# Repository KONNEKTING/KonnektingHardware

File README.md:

# KonnektingHardware
Schematics and pcb layouts for KONNEKTING devices

There's no common license for all KONNEKTING hardware. Please check each sub-folder for its license.

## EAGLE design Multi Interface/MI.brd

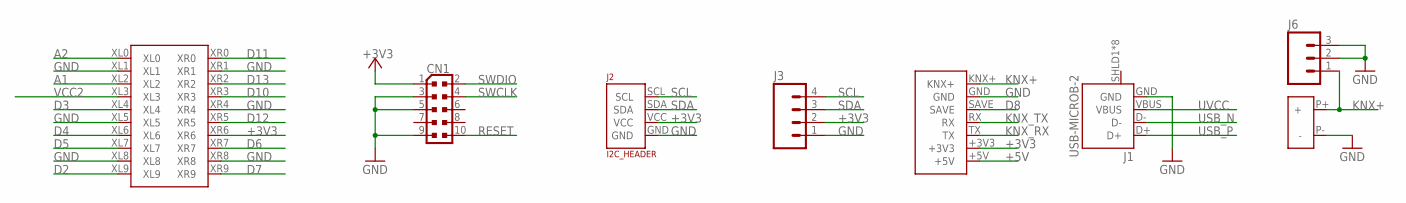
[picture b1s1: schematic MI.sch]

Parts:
CN1: 0171_PH127-205DF055G00AROUND-PADS; PINHEAD_2X05_127
J1: USB-MICROB-2; USB-MICROB-10118194
J2: I2C_HEADER; 4_2.54_11.8X10.2MM
J3: M04NO_SILK_ALL_ROUND; 1X04_NO_SILK_ALL_ROUND
J6: M031X03_NO_SILK; 1X03_NO_SILK
U$1: UFI2; UFI_34X34MM
U$2: KNX_KLEMME
U$3: MICRO_BCU_7_2.54DOCU_D1.4; MICRO_BCU_7_2.54_D1.4_DOCU

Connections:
+3V3: CN1.1, J2.VCC, J3.2, U$1.XR6, U$3.+3V3
+5V: U$3.+5V
A1: U$1.XL2
A2: U$1.XL0
D2: U$1.XL9
D3: U$1.XL4
D4: U$1.XL6
D5: U$1.XL7
D6: U$1.XR7
D7: U$1.XR9
D8: U$3.SAVE
D10: U$1.XR3
D11: U$1.XR0
D12: U$1.XR5
D13: U$1.XR2
GND: CN1.3, CN1.5, CN1.9, J1.GND, J2.GND, J3.1, J6.2, J6.3, U$1.XL1, U$1.XL5, U$1.XL8, U$1.XR1, U$1.XR4, U$1.XR8, U$2.P- (-), U$3.GND
KNX+: J6.1, U$2.P+ (+), U$3.KNX+
KNX_RX: U$3.TX
KNX_TX: U$3.RX
RESET: CN1.10
SCL: J2.SCL, J3.4
SDA: J2.SDA, J3.3
SWCLK: CN1.4
SWDIO: CN1.2
USB_N: J1.D-
USB_P: J1.D+
UVCC: J1.VBUS
VCC2: U$1.XL3

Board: 2 copper layers, 8 parts (3 on the bottom side), 5 nets, no tracks yet.

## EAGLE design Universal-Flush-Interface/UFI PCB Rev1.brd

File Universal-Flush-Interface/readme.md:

# Universal UP Schnittstelle

english version: [readme_en.md](/Universal-Flush-Interface/readme_en.md)

## Lizenz

Die Hardware und Doku dieser Schnittstelle stehen unter folgender Lizenz: [license.md](/Universal-Flush-Interface/license.md)

## Weitere Informationen
[KNX User Forum] (https://knx-user-forum.de/forum/projektforen/konnekting/941633-universal-up-schnittstelle-1wire-up-mini-gateway-bin%C3%A4reing%C3%A4nge-i%C2%B2c-spi-digitale-i-os-etc)

## Teile

|Shop       | Bauteil  | Anzahl | Bestellnummer  |Bezeichnung             |
|:----------|:---------|:-------|:---------------|:-----------------------|
|	Digikey	|	C1,C2	|	2	|	399-8269-1-ND	|	CAP TANT 10UF 16V 10% 1206	|
|	Digikey	|	C32	|	1	|	493-2203-1-ND	|	CAP ALUM 100UF 20% 35V SMD	|
|	Digikey	|	C34	|	3	|	1276-1861-1-ND	|	CAP CER 1UF 35V X5R 0603	|
|	Digikey	|	C35	|	1	|	399-7927-1-ND	|	CAP CER 4700PF 25V X7R 0603	|
|	Digikey	|	C36	|	1	|	1276-1063-1-ND	|	CAP CER 0.047UF 50V X7R 0603	|
|	Digikey	|	C39	|	1	|	2 1276-2407-1-ND	|	CAP CER 10UF 6.3V X5R 0805	|
|	Digikey	|	C4,C5,C21,C31,C37,C38	|	6	|	399-7845-1-ND	|	CAP CER 0.1UF 50V X7R 0603	|
|	Digikey	|	D31	|	1	|	SS16T3GOSCT-ND	|	DIODE SCHOTTKY 60V 1A SMA	|
|	Digikey	|	D32	|	1	|	1SMA40CAT3GOSCT-ND	|	TVS DIODE 40VWM 64.5VC SMA	|
|	Digikey	|	ATMEGA32U4	|	1	|	ATMEGA32U4-MU-ND	|	IC MCU 8BIT 32KB FLASH 44QFN	|
|	Digikey	|	L1	|	1	|	SRR4028-221YCT-ND	|	FIXED IND 220UH 340MA 1.25 OHM	|
|	Digikey	|	Lötstifte	|	2	|	36-1425-2-ND	|	CONN PC PIN CIRC 0.040DIA TIN	|
|	Digikey	|	NCN5120	|	1	|	NCN5120MNTWGOSCT-ND	|	IC RECEIVER/XMITTER KNX 40QFN	|
|	Digikey	|	PROG_LED	|	1	|	475-2815-1-ND	|	LED BLUE DIFFUSED 0603 SMD	|
|	Digikey	|	PROG_SW	|	1	|	450-2146-1-ND	|	SWITCH TACTILE SPST-NO 0.05A 24V	|
|	Digikey	|	R1,R24	|	2	|	RNCP0603FTD10K0CT-ND	|	RES SMD 10K OHM 1% 1/8W 0603	|
|	Digikey	|	R2,R3	|	2	|	311-22.0HRCT-ND	|	RES SMD 22 OHM 1% 1/10W 0603	|
|	Digikey	|	R21	|	1	|	RNCP0603FTD100RCT-ND	| RES SMD 100 OHM 1% 1/8W 0603  |
|	Digikey	|	R22,R23,R26,R27	|	4	|	311-4.70KHRCT-ND	|	RES SMD 4.7K OHM 1% 1/10W 0603	|
|	Digikey	|	R25	|	1	|	311-1.00KHRCT-ND	|	RES SMD 1K OHM 1% 1/10W 0603	|
|	Digikey	|	R35	|	1	|	5 A102515CT-ND	|	RES SMD 22 OHM 5% 1W 2512	|
|	Digikey	|	R36	|	1	|	RNCP0603FTD1R00CT-ND	|	RES SMD 1 OHM 1% 1/8W 0603	|
|	Digikey	|	U1	|	1	|	576-1281-1-ND	|	IC REG LDO 3.3V 0.5A SOT23-5	|
|	Digikey	|	USB	|	1	|	609-4618-1-ND	|	USB - Mikro-B, USB 2,0	|
|	Digikey	|	Y1	|	1	|	490-1195-1-ND	|	CER RES 8.0000MHZ 33PF SMD	|
|	Digikey	|	Y31	|	1	|	490-1198-1-ND	|	CER RES 16.0000MHZ 15PF SMD	|
|	Conrad	|		|	1	|	534298	|	Gehäuse 40x40x20	|
|	Conrad	|		|	2	|	889177	|	Schraube 2.2x4.5mm	|
|	Conrad	|		|	1	|	567891	|	Schraubklemme 10polig	|
|		|		|		|		|		|
|	Conrad	|		|	1+1*	|	567615	|	Schraubklemme 3polig	|
|		|		|		|		|		|
|	Conrad	|		|	1*	|	1088238	|	Stiftleiste	|
|	Conrad	|		|	1*	|	1088237	|	Buchse	|
|	Conrad	|		|	4*	|	1088222	|	Crimpkontakt	|
|		|		|		|		|		|
|	Conrad	|		|	1*	|	567803	|	Schraubklemme 7polig	|
|	Conrad	|		|	1*	|	567658	|	Schraubklemme 4polig	|

*) Man kann zwischen 3 Optionen wählen
- 3-polige Schraubklemme + Stiftleiste/Buchse/Crimpkontakt 
- 3+4-polige Schraubklemme
- 7-polige Schraubklemme

## Schaltung
[Universal Flush Interface.pdf](/Universal-Flush-Interface/Universal Flush Interface.pdf)

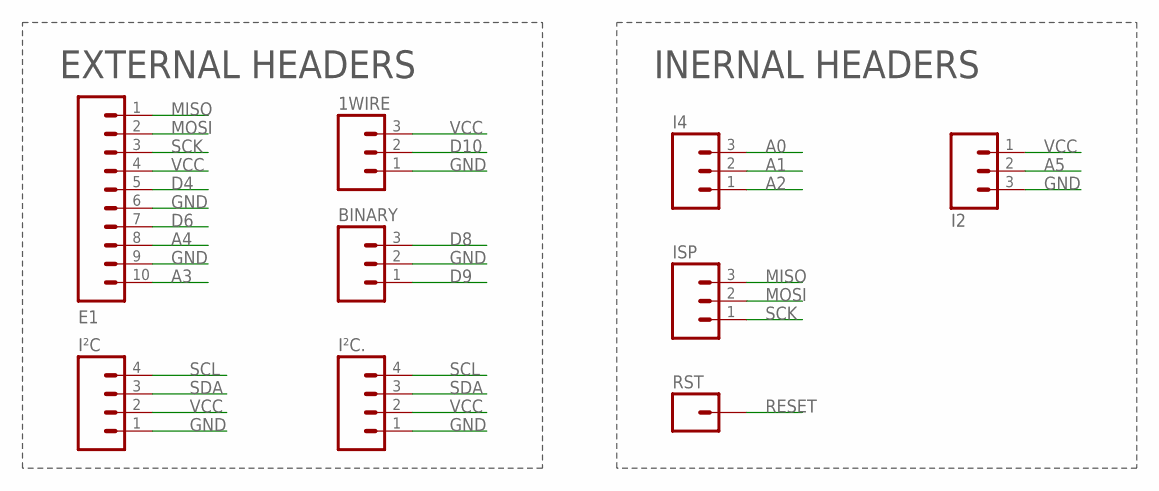
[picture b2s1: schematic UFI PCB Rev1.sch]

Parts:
1WIRE: M031X03_NO_SILK; 1X03_NO_SILK
BINARY: M031X03_NO_SILK; 1X03_NO_SILK
E1: M10NO_SILK_PTH_FEMALE; 1X10_NO_SILK
I2, I4: M031X03_NO_SILK; 1X03_NO_SILK
ISP: M031X03_NO_SILK; 1X03_NO_SILK
I²C, I²C.: M04NO_SILK_ALL_ROUND; 1X04_NO_SILK_ALL_ROUND
RST: M01PTH_NO_SILK_YES_STOP; 1X01_NO_SILK

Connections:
A0: I4.3
A1: I4.2
A2: I4.1
A3: E1.10
A4: E1.8
A5: I2.2
D4: E1.5
D6: E1.7
D8: BINARY.3
D9: BINARY.1
D10: 1WIRE.2
GND: 1WIRE.1, BINARY.2, E1.6, E1.9, I2.3, I²C.1, I²C..1
MISO: E1.1, ISP.3
MOSI: E1.2, ISP.2
RESET: RST.1
SCK: E1.3, ISP.1
SCL: I²C.4, I²C..4
SDA: I²C.3, I²C..3
VCC: 1WIRE.3, E1.4, I2.1, I²C.2, I²C..2

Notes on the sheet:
EXTERNAL HEADERS
INERNAL HEADERS

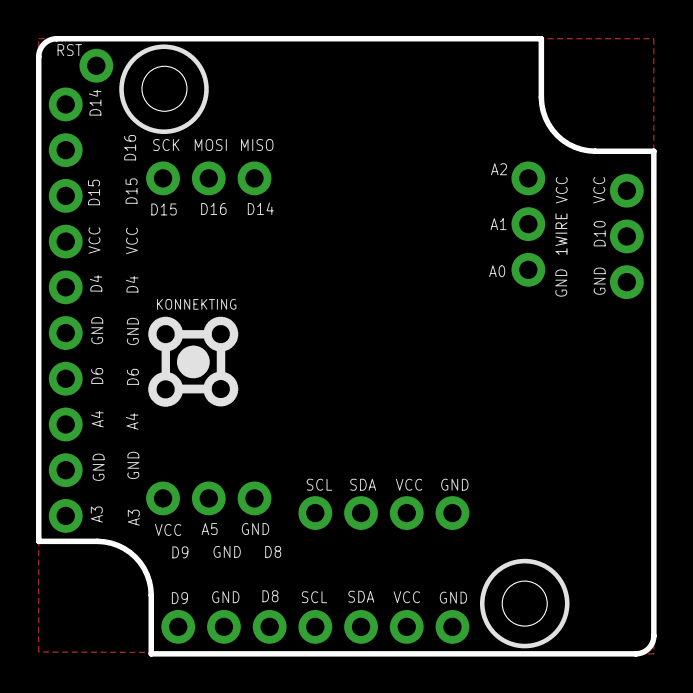
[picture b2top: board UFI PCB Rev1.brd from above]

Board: 2 copper layers, 34.2 x 34.2 mm, 10 parts (0 on the bottom side), 7 nets.

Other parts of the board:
U$1: LOGO_5MM

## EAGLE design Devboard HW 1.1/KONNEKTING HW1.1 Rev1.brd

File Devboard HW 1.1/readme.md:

# Devboard HW 1.1

## License

Hardware and documentation released under this license: [license.md](/Devboard HW 1.1/license.md)

## More infos: 
[konnekting.de](http://www.konnekting.de/projekte/entwicklungsboards/)

## Parts

|Article number        | Part  | Description         | Amount      |
|:------------------|:---------|:--------------------|:-------------|
|	493-2203-1-ND 	|	C7 	|	CAP ALUM 100UF 20% 35V SMD 	|	1	|
|	1276-1063-1-ND 	|	C4 	|	CAP CER 0.047UF 50V X7R 0603 	|	1	|
|	399-7845-1-ND 	|	C6;C9;C11;C15 	|	CAP CER 0.1UF 50V X7R 0603 	|	4	|
|	1276-3013-1-ND 	|	C1;C12 	|	CAP CER 10UF 6.3V Y5V 0805 	|	2	|
|	1276-1861-1-ND 	|	C8 	|	CAP CER 1UF 35V X5R 0603 	|	1	|
|	399-7927-1-ND 	|	C5 	|	CAP CER 4700PF 25V X7R 0603 	|	1	|
|	490-1198-1-ND 	|	Y1 	|	CER RES 16.0000MHZ 15PF SMD 	|	1	|
|	36-1425-2-ND 	|	Pins	|	CONN PC PIN CIRC 0.040DIA TIN 	|	2	|
|	SS16T3GOSCT-ND 	|	D1 	|	DIODE SCHOTTKY 60V 1A SMA 	|	1	|
|	SRR5028-221YCT-ND 	|	L1;L2 	|	FIXED IND 220UH 300MA 1.25 OHM 	|	2	|
|	NCN5120MNTWGOSCT-ND 	|	NCN5120 	|	IC RECEIVER/XMITTER KNX 40QFN 	|	1	|
|	475-2815-1-ND 	|	PROG_LED 	|	LED BLUE DIFFUSED 0603 SMD 	|	1	|
|	RNCP0603FTD1R00CT-ND 	|	R2;R5 	|	RES SMD 1 OHM 1% 1/8W 0603 	|	2	|
|	RNCP0603FTD100RCT-ND 	|	R10_LED_3.3V 	|	RES SMD 100 OHM 1% 1/8W 0603 	|	1	|
|	RNCP0603FTD475RCT-ND 	|	R10_LED_5V 	|	RES SMD 475 OHM 1% 1/8W 0603 	|	1	|
|	RNCP0603FTD10K0CT-ND 	|	R13 	|	RES SMD 10K OHM 1% 1/8W 0603 	|	1	|
|	311-33.0KHRCT-ND 	|	R3_5V 	|	RES SMD 33K OHM 1% 1/10W 0603 	|	1	|
|	311-180KHRCT-ND 	|	R6_5V 	|	RES SMD 180K OHM 1% 1/10W 0603 	|	1	|
|	RNCP0603FTD1K00CT-ND 	|	R7,R8,R9 	|	RES SMD 1K OHM 1% 1/8W 0603 	|	3	|
|	A102515CT-ND 	|	R4 	|	RES SMD 22 OHM 5% 1W 2512 	|	1	|
|	RNCP0603FTD2K00CT-ND 	|	R12 	|	RES SMD 2K OHM 1% 1/8W 0603 	|	1	|
|	311-4.70KHRCT-ND 	|	R1_1WIRE 	|	RES SMD 4.7K OHM 1% 1/10W 0603 	|	1	|
|	450-2146-1-ND 	|	PROG_SW 	|	SWITCH TACTILE SPST-NO 0.05A 24V 	|	1	|
|	1SMA40CAT3GOSCT-ND 	|	D2 	|	TVS DIODE 40VWM 64.5VC SMA 	|	1	|

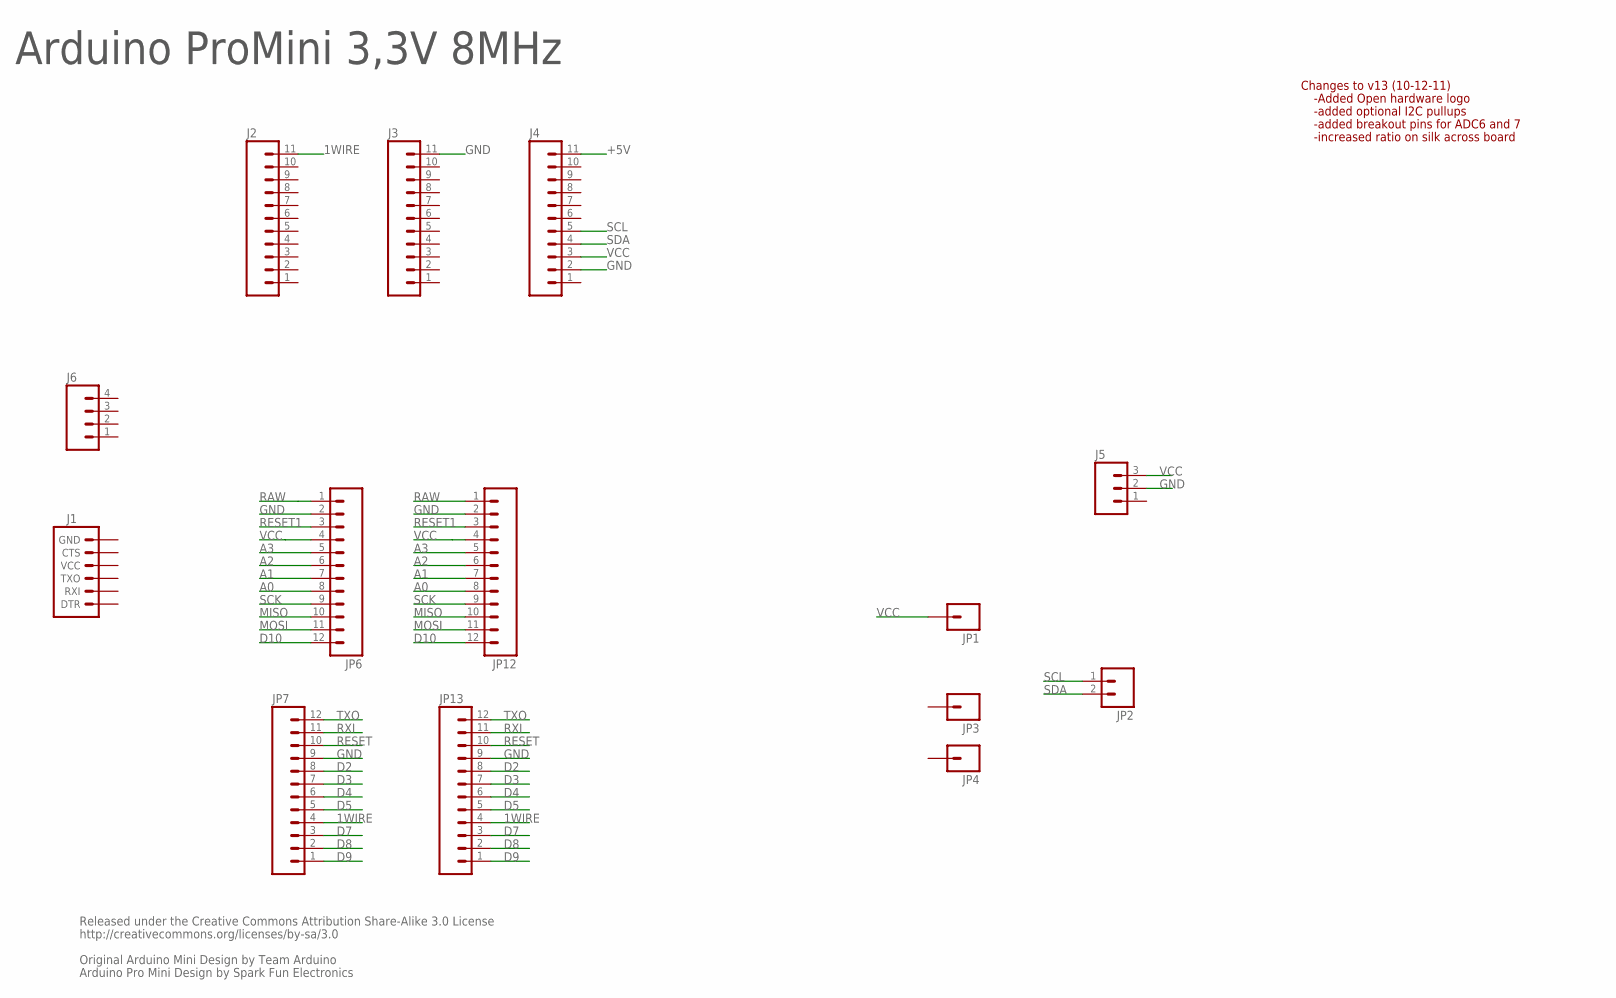
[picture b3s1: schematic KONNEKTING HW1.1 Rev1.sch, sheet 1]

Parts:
J1: ARDUINO_SERIAL_PROGRAMPTH; 1X06
J2, J3, J4: M11PTH; 1X11
J5: M03PTH; 1X03
J6: M04PTH; 1X04
JP1, JP3, JP4: M01PTH; 1X01
JP2: M02PTH; 1X02
JP6, JP7, JP12, JP13: M12PTH; 1X12

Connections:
1WIRE: J2.11, JP7.4, JP13.4; also elsewhere on the board
+5V: J4.11; also elsewhere on the board
A0: JP6.8, JP12.8
A1: JP6.7, JP12.7
A2: JP6.6, JP12.6
A3: JP6.5, JP12.5
D2: JP7.8, JP13.8; also elsewhere on the board
D3: JP7.7, JP13.7; also elsewhere on the board
D4: JP7.6, JP13.6
D5: JP7.5, JP13.5
D7: JP7.3, JP13.3; also elsewhere on the board
D8: JP7.2, JP13.2; also elsewhere on the board
D9: JP7.1, JP13.1; also elsewhere on the board
D10: JP6.12, JP12.12
GND: J3.11, J4.2, J5.2, JP6.2, JP7.9, JP12.2, JP13.9; also elsewhere on the board
MISO: JP6.10, JP12.10
MOSI: JP6.11, JP12.11
RAW: JP6.1, JP12.1
RESET: JP7.10, JP13.10
RESET1: JP6.3, JP12.3
RXI: JP7.11, JP13.11; also elsewhere on the board
SCK: JP6.9, JP12.9
SCL: J4.5, JP2.1
SDA: J4.4, JP2.2
TXO: JP7.12, JP13.12; also elsewhere on the board
VCC: J4.3, J5.3, JP1.1, JP6.4, JP12.4; also elsewhere on the board

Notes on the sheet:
Released under the Creative Commons Attribution Share-Alike 3.0 License
http://creativecommons.org/licenses/by-sa/3.0
Original Arduino Mini Design by Team Arduino
Arduino Pro Mini Design by Spark Fun Electronics
Changes to v13 (10-12-11)
-Added Open hardware logo
-added optional I2C pullups
-added breakout pins for ADC6 and 7
-increased ratio on silk across board
Arduino ProMini 3,3V 8MHz

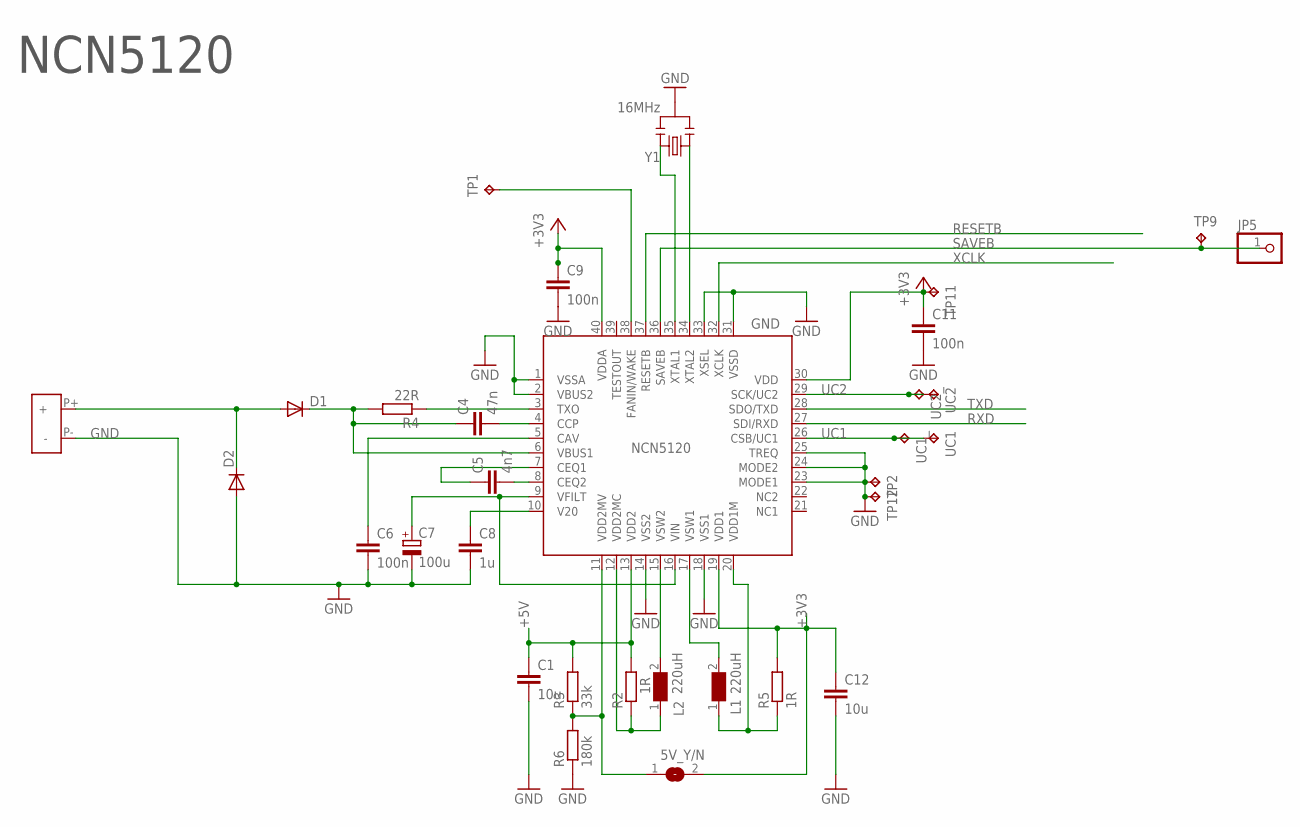
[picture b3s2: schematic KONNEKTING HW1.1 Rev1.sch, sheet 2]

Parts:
5V_Y/N: SJ
C1, C12: 10u; C0805
C4: 47n; C0603
C5: 4n7; C0603
C6, C9, C11: 100n; C0603
C7: 100u; UD-6,3X7,7_NICHICON
C8: 1u; C0603
D1, D2: DIODESMA-ALT; SMA-DIODE_ALT
GND: NCN5120_KNX_TRANSCEIVER; QFN40
JP5: PINHD-1X1; 1X01
L1, L2: 220uH; WE-PD2_7850
R2, R5: 1R; R0603
R3: 33k; R0603
R4: 22R; R2512
R6: 180k; R0603
TP1, TP9: TPTP10SQ; TP10SQ
TP2, TP11, TP12: TPTP09SQ; TP09SQ
U$2: KNX_KLEMME
UC1, UC1_, UC2, UC2_: TPTP09SQ; TP09SQ
Y1: 16MHz; RESONATOR-SMD

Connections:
+3V3: 5V_Y/N.2, C9.1, C11.1, C12.1, GND.19 (VDD1), GND.30 (VDD), GND.40 (VDDA), R5.2, TP11.TP; also elsewhere on the board
+5V: C1.1, GND.13 (VDD2), R2.2, R3.2; also elsewhere on the board
GND: C1.2, C6.2, C7.-, C8.2, C9.2, C11.2, C12.2, D2.A, GND.1 (VSSA), GND.2 (VBUS2), GND.14 (VSS2), GND.18 (VSS1), GND.23 (MODE1), GND.24 (MODE2), GND.25 (TREQ), GND.31 (VSSD), GND.33 (XSEL), R6.1, TP2.TP, TP12.TP, U$2.P- (-), Y1.2; also elsewhere on the board
unnamed: 5V_Y/N.1, GND.11 (VDD2MV), R3.1, R6.2
unnamed: GND.3 (TXO), R4.1
unnamed: C4.1, D1.C, GND.6 (VBUS1), R4.2
unnamed: C5.1, GND.7 (CEQ1)
unnamed: C7.+, GND.9 (VFILT), GND.16 (VIN)
unnamed: GND.15 (VSW2), L2.2
unnamed: C8.1, GND.10 (V20)
unnamed: C6.1, GND.5 (CAV)
unnamed: C4.2, GND.4 (CCP)
unnamed: C5.2, GND.8 (CEQ2)
unnamed: D1.A, D2.C, U$2.P+ (+)
unnamed: GND.38 (FANIN/WAKE), TP1.TP
unnamed: GND.12 (VDD2MC), L2.1, R2.1
unnamed: GND.35 (XTAL1), Y1.3
unnamed: GND.34 (XTAL2), Y1.1
unnamed: GND.17 (VSW1), L1.2
unnamed: GND.20 (VDD1M), L1.1, R5.1
RESETB: GND.37 (RESETB)
RXD: GND.27 (SDI/RXD); also elsewhere on the board
SAVEB: GND.36 (SAVEB), JP5.1, TP9.TP
TXD: GND.28 (SDO/TXD); also elsewhere on the board
UC1: GND.26 (CSB/UC1), UC1.TP, UC1_.TP
UC2: GND.29 (SCK/UC2), UC2.TP, UC2_.TP
XCLK: GND.32 (XCLK)

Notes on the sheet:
NCN5120

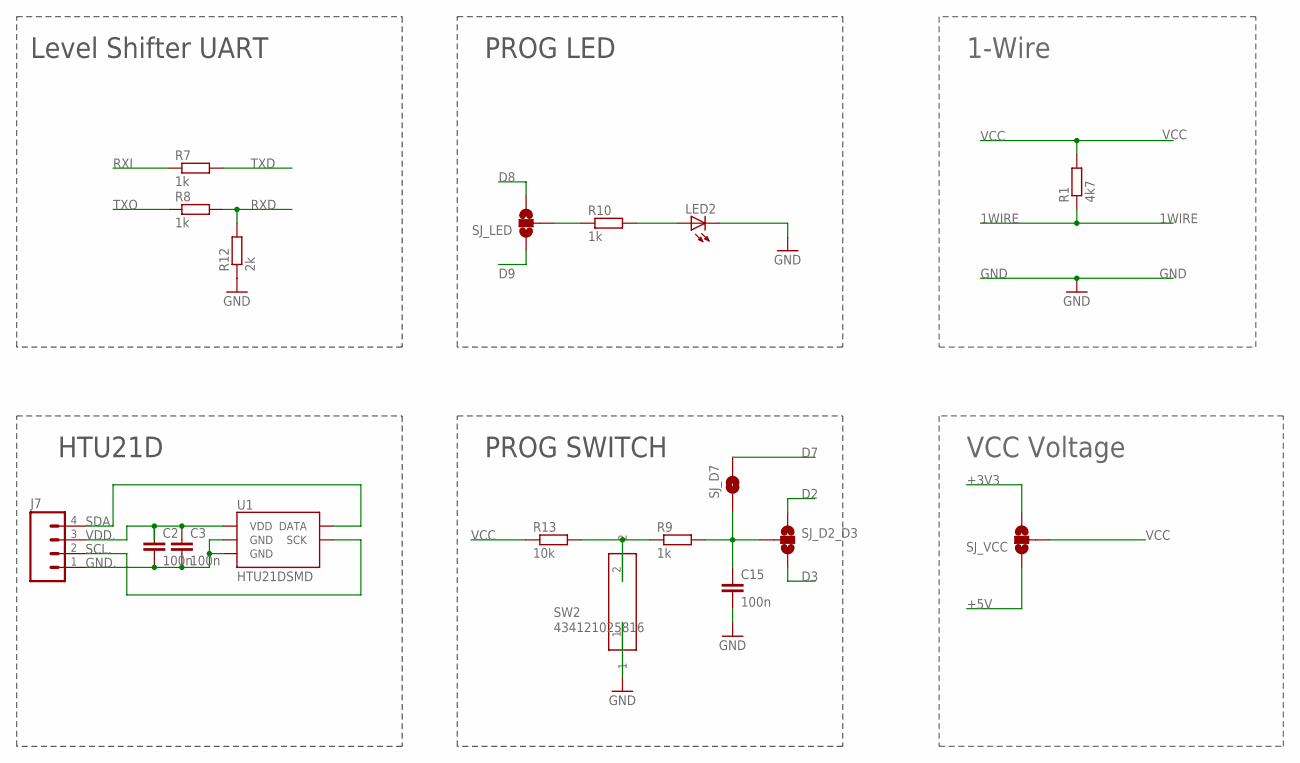
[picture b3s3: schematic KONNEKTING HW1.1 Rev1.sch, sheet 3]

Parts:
C2, C3: 100n; 0603-CAP
C15: 100n; C0603
J7: M04PTH; 1X04
LED2: LEDCHIP-LED0805; CHIP-LED0805
R1: 4k7; R0603
R7, R8: 1k; R0805
R9, R10: 1k; R0603
R12: 2k; R0805
R13: 10k; R0603
SJ_D2_D3: SOLDERJUMPER_2WAYS; SJ_3
SJ_D7: SOLDERJUMPERNO; SJ_2S-NO
SJ_LED: SOLDERJUMPER_2WAYS; SJ_3
SJ_VCC: SOLDERJUMPER_2WAYS; SJ_3
SW2: 434121025816
U1: HTU21DSMD; HTU21D

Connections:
1WIRE: R1.1; also elsewhere on the board
+3V3: SJ_VCC.3; also elsewhere on the board
+5V: SJ_VCC.1; also elsewhere on the board
D2: SJ_D2_D3.1; also elsewhere on the board
D3: SJ_D2_D3.3; also elsewhere on the board
D7: SJ_D7.2; also elsewhere on the board
D8: SJ_LED.3; also elsewhere on the board
D9: SJ_LED.1; also elsewhere on the board
GND: C15.2, LED2.C, R12.1, SW2.1; also elsewhere on the board
GND.: C2.2, C3.2, J7.1, U1.7 (GND), U1.GND
unnamed: R9.1, R13.2, SW2.2
unnamed: LED2.A, R10.2
unnamed: R10.1, SJ_LED.2
unnamed: C15.1, R9.2, SJ_D2_D3.2, SJ_D7.1
RXD: R8.2, R12.2; also elsewhere on the board
RXI: R7.1; also elsewhere on the board
SCL.: J7.2, U1.SCK
SDA.: J7.4, U1.DATA
TXD: R7.2; also elsewhere on the board
TXO: R8.1; also elsewhere on the board
VCC: R1.2, R13.1, SJ_VCC.2; also elsewhere on the board
VDD.: C2.1, C3.1, J7.3, U1.VDD

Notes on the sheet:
Level Shifter UART
PROG LED
HTU21D
PROG SWITCH
1-Wire
VCC Voltage

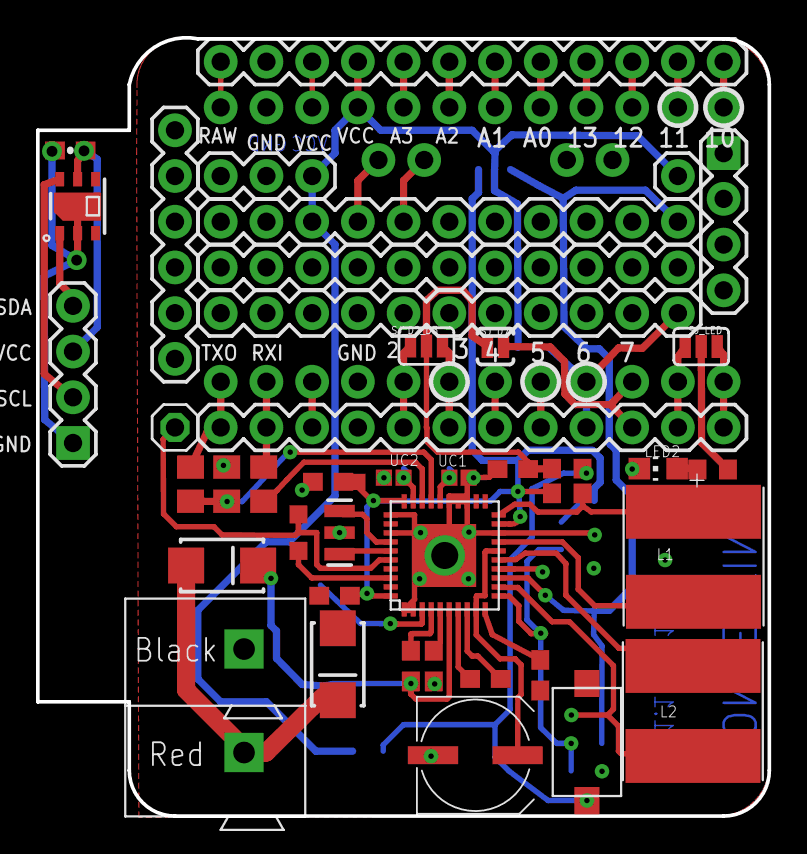
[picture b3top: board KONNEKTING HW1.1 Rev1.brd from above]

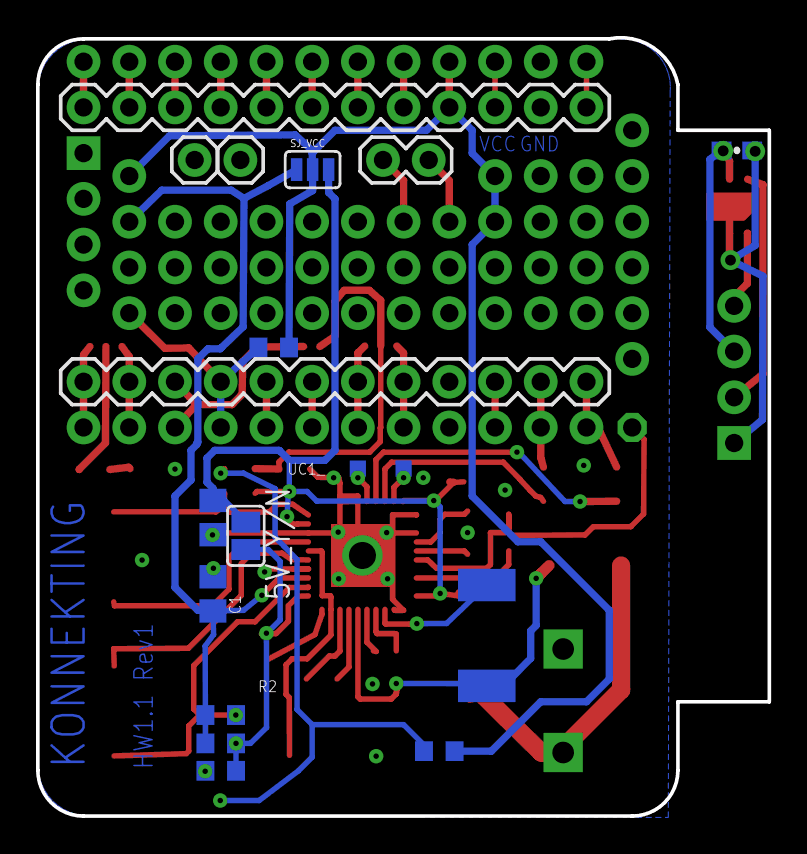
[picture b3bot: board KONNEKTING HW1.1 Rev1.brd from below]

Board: 2 copper layers, 40.6 x 43.2 mm, 64 parts (18 on the bottom side), 57 nets.

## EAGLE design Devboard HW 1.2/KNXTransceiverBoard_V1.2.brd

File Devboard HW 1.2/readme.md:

# Devboard HW 1.2

## License

Hardware and documentation released under this license: [license.md](/Devboard HW 1.2/license.md)

## More infos: 
[konnekting.de](http://www.konnekting.de/projekte/entwicklungsboards/)

## Parts for NCN5120
|Article number        | Part  | Description         | Amount      |
|:------------------|:---------|:--------------------|:-------------|
|	493-2203-1-ND	|	C11	|	CAP ALUM 100UF 20% 35V SMD	|	1	|
|	1276-1063-1-ND	|	C7	|	CAP CER 0.047UF 50V X7R 0603	|	1	|
|	399-7845-1-ND	|	C9;C18;C20;C21	|	CAP CER 0.1UF 50V X7R 0603	|	4	|
|	1276-2407-1-ND	|	C15	|	CAP CER 10UF 6.3V X5R 0805	|	1	|
|	1276-1861-1-ND	|	C4	|	CAP CER 1UF 35V X5R 0603	|	1	|
|	399-7927-1-ND	|	C8	|	CAP CER 4700PF 25V X7R 0603	|	1	|
|	490-1198-1-ND	|	Y1	|	CER RES 16.0000MHZ 15PF SMD	|	1	|
|	36-1425-2-ND	|	Pins	|	CONN PC PIN CIRC 0.040DIA TIN	|	2	|
|	SS16T3GOSCT-ND	|	D1	|	DIODE SCHOTTKY 60V 1A SMA	|	1	|
|	SRR5028-221YCT-ND	|	L1	|	FIXED IND 220UH 300MA 1.25 OHM	|	1	|
|	NCN5120MNTWGOSCT-ND	|	NCN5120	|	IC RECEIVER/XMITTER KNX 40QFN	|	1	|
|	475-2815-1-ND	|	PROG_LED	|	LED BLUE DIFFUSED 0603 SMD	|	1	|
|	RNCP0603FTD1R00CT-ND	|	R3	|	RES SMD 1 OHM 1% 1/8W 0603	|	1	|
|	RNCP0603FTD100RCT-ND	|	R123.3V	|	RES SMD 100 OHM 1% 1/8W 0603	|	1	|
|	RNCP0603FTD10K0CT-ND	|	R14	|	RES SMD 10K OHM 1% 1/8W 0603	|	1	|
|	311-1.00KHRCT-ND	|	R8;R9;R10	|	RES SMD 1K OHM 1% 1/10W 0603	|	3	|
|	A102515CT-ND	|	R1	|	RES SMD 22 OHM 5% 1W 2512	|	1	|
|	450-2146-1-ND	|	PROG_SW	|	SWITCH TACTILE SPST-NO 0.05A 24V	|	1	|
|	1SMA40CAT3GOSCT-ND	|	D2	|	TVS DIODE 40VWM 64.5VC SMA	|	1	|

## Parts for ProMicro

|Article number        | Part  | Description         | Amount      |
|:------------------|:---------|:--------------------|:-------------|
|	399-7845-1-ND 	|	C1;C2;C3 	|	CAP CER 0.1UF 50V X7R 0603 	|	3	|
|	1276-1036-1-ND 	|	C5;C10 	|	CAP CER 1UF 6.3V X5R 0603 	|	2	|
|	399-8269-1-ND 	|	C13;C19 	|	CAP TANT 10UF 16V 10% 1206 	|	2	|
|	490-1195-1-ND 	|	Y3 	|	CER RES 8.0000MHZ 33PF SMD 	|	1	|
|	732-3155-1-ND 	|	USB 	|	CONN RCPT USB MICRO B R/A SMT 	|	1	|
|	NSR0320MW2T1GOSCT-ND 	|	D2 	|	DIODE SCHOTTKY 20V 1A SOD323 	|	1	|
|	507-1876-1-ND 	|	F1 	|	FUSE 500MA 125VAC FAST 1206 	|	1	|
|	ATMEGA32U4-MU-ND 	|	IC 	|	IC MCU 8BIT 32KB FLASH 44QFN 	|	1	|
|	576-1281-1-ND 	|	U2 	|	IC REG LDO 3.3V 0.5A SOT23-5 	|	1	|
|	475-2815-1-ND 	|	LED1 	|	LED BLUE DIFFUSED 0603 SMD 	|	1	|
|	475-2709-1-ND 	|	GREEN 	|	LED GREEN DIFFUSED 0603 SMD 	|	1	|
|	475-1196-1-ND 	|	YELLOW 	|	LED YELLOW DIFFUSED 0603 SMD 	|	1	|
|	RNCP0603FTD100RCT-ND 	|	R11 	|	RES SMD 100 OHM 1% 1/8W 0603 	|	1	|
|	311-10.0KHRCT-ND 	|	R2 	|	RES SMD 10K OHM 1% 1/10W 0603 	|	1	|
|	311-1.0KGRCT-ND 	|	R4;R6 	|	RES SMD 1K OHM 5% 1/10W 0603 	|	2	|
|	311-22.0HRCT-ND 	|	R5;R7 	|	RES SMD 22 OHM 1% 1/10W 0603 	|	2	|
|	CKN9104CT-ND 	|	ResetBtn 	|	SWITCH TACTILE SPST-NO 0.02A 15V 	|	1	|

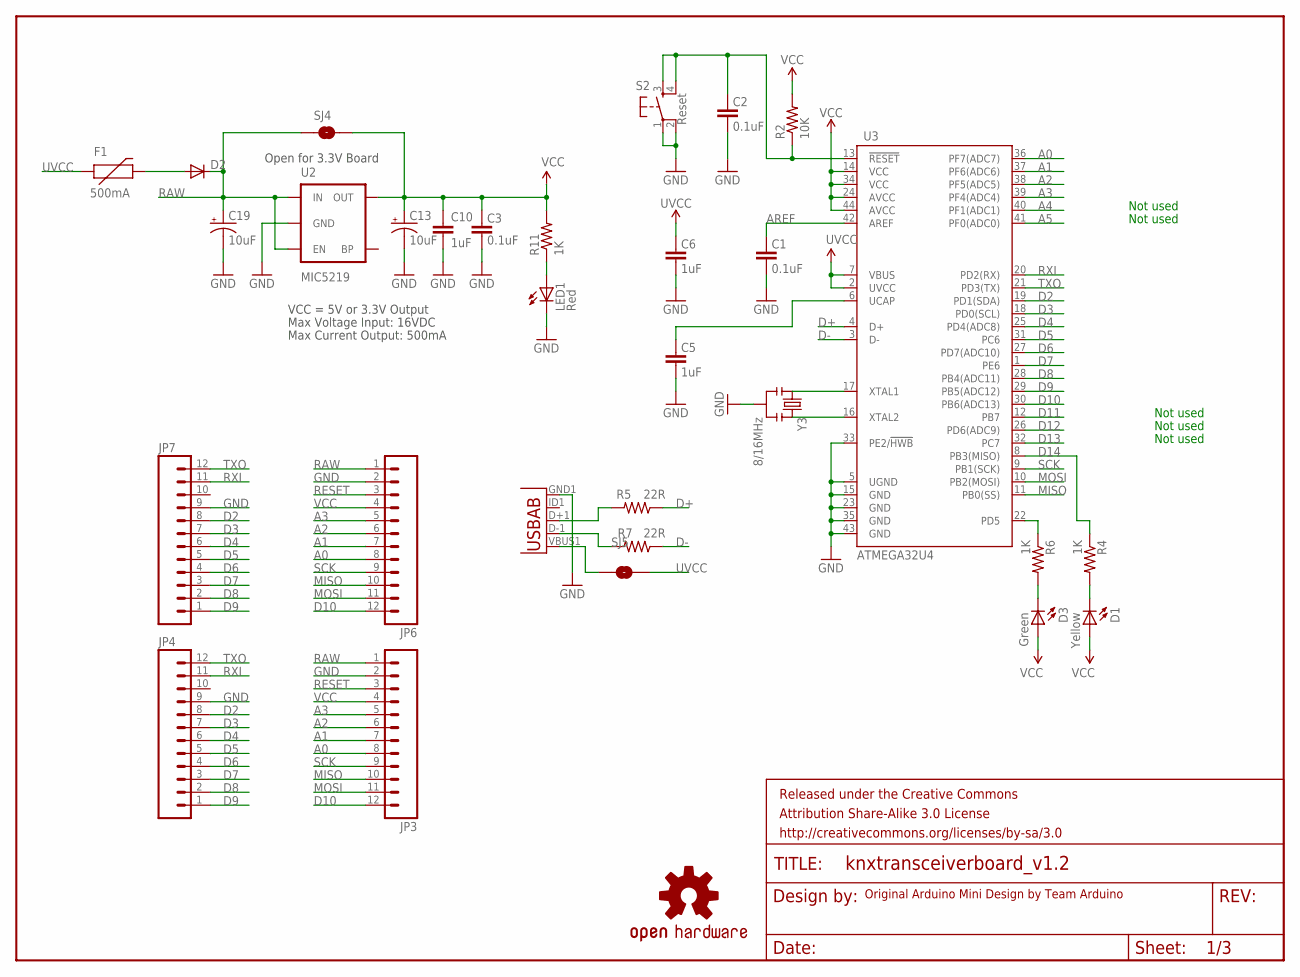
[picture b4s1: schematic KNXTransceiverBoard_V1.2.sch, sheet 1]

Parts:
C1, C2, C3: 0.1uF; 0603-CAP
C5, C6, C10: 1uF; 0603-CAP
C13, C19: 10uF; EIA3216
D1: Yellow; LED-0603
D2: DIODESOD; SOD-323
D3: Green; LED-0603
F1: 500mA; PTC-1206
FRAME1: FRAME-LETTER; CREATIVE_COMMONS
JP3, JP4, JP6, JP7: M12PTH; 1X12
LED1: Red; LED-0603
R2: 10K; 0603-RES
R4, R6, R11: 1K; 0603-RES
R5, R7: 22R; 0603-RES
S2: Reset; TACTILE_SWITCH_SMD
SJ4, SJ5: SOLDERJUMPERNC; SJ_2S
U2: MIC5219; SOT23-5
U3: ATMEGA32U4; QFN-44-NOPAD_1:1-OUTFAKES
U$3: OSHW-LOGOS; OSHW-LOGO-S
X1: USB-ABIN&OUT; USB-AB-MICRO-SMD-V03-IN&OUT
Y3: 8/16MHz; RESONATOR-SMD

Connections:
A0: JP3.8, JP6.8, U3.36 (PF7(ADC7))
A1: JP3.7, JP6.7, U3.37 (PF6(ADC6))
A2: JP3.6, JP6.6, U3.38 (PF5(ADC5))
A3: JP3.5, JP6.5, U3.39 (PF4(ADC4))
A4: U3.40 (PF1(ADC1))
A5: U3.41 (PF0(ADC0))
AREF: C1.2, U3.42 (AREF)
D2: JP4.8, JP7.8, U3.19 (PD1(SDA)); also elsewhere on the board
D3: JP4.7, JP7.7, U3.18 (PD0(SCL)); also elsewhere on the board
D4: JP4.6, JP7.6, U3.25 (PD4(ADC8))
D5: JP4.5, JP7.5, U3.31 (PC6)
D6: JP4.4, JP7.4, U3.27 (PD7(ADC10))
D7: JP4.3, JP7.3, U3.1 (PE6); also elsewhere on the board
D8: JP4.2, JP7.2, U3.28 (PB4(ADC11)); also elsewhere on the board
D9: JP4.1, JP7.1, U3.29 (PB5(ADC12))
D10: JP3.12, JP6.12, U3.30 (PB6(ADC13))
D11: U3.12 (PB7)
D12: U3.26 (PD6(ADC9))
D13: U3.32 (PC7)
D14: R4.1, U3.8 (PB3(MISO))
D+: R5.1, U3.4 (D+)
D-: R7.1, U3.3 (D-)
GND: C1.1, C2.1, C3.1, C5.1, C6.1, C10.2, C13.C (-), C19.C (-), JP3.2, JP4.9, JP6.2, JP7.9, LED1.C, S2.1, S2.2, U2.2 (GND), U3.5 (UGND), U3.15 (GND), U3.23 (GND), U3.33 (PE2/!HWB), U3.35 (GND), U3.43 (GND), X1.GND1 (GND), Y3.2; also elsewhere on the board
MISO: JP3.10, JP6.10, U3.11 (PB0(SS))
MOSI: JP3.11, JP6.11, U3.10 (PB2(MOSI))
unnamed: U3.16 (XTAL2), Y3.3
unnamed: U3.17 (XTAL1), Y3.1
unnamed: C5.2, U3.6 (UCAP)
unnamed: D1.C, R4.2
unnamed: R7.2, X1.D-1 (D-)
unnamed: D3.C, R6.2
unnamed: R5.2, X1.D+1 (D+)
unnamed: D2.2 (A), F1.2
unnamed: LED1.A, R11.1
RAW: C19.A (+), D2.1 (C), JP3.1, JP6.1, SJ4.1, U2.1 (IN), U2.3 (EN); also elsewhere on the board
RESET: C2.2, JP3.3, JP6.3, R2.1, S2.3, S2.4, U3.13 (!RESET)
RXI: JP4.11, JP7.11, U3.20 (PD2(RX)); also elsewhere on the board
SCK: JP3.9, JP6.9, U3.9 (PB1(SCK))
TXLED: R6.1, U3.22 (PD5)
TXO: JP4.12, JP7.12, U3.21 (PD3(TX)); also elsewhere on the board
UVCC: C6.2, F1.1, SJ5.2, U3.2 (UVCC), U3.7 (VBUS)
VBUS1: SJ5.1, X1.VBUS1 (VBUS)
VCC: C3.2, C10.1, C13.A (+), D1.A, D3.A, JP3.4, JP6.4, R2.2, R11.2, SJ4.2, U2.5 (OUT), U3.14 (VCC), U3.24 (AVCC), U3.34 (VCC), U3.44 (AVCC); also elsewhere on the board

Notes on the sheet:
Original Arduino Mini Design by Team Arduino
Max Voltage Input: 16VDC
Max Current Output: 500mA
VCC = 5V or 3.3V Output
Not used
Open for 3.3V Board

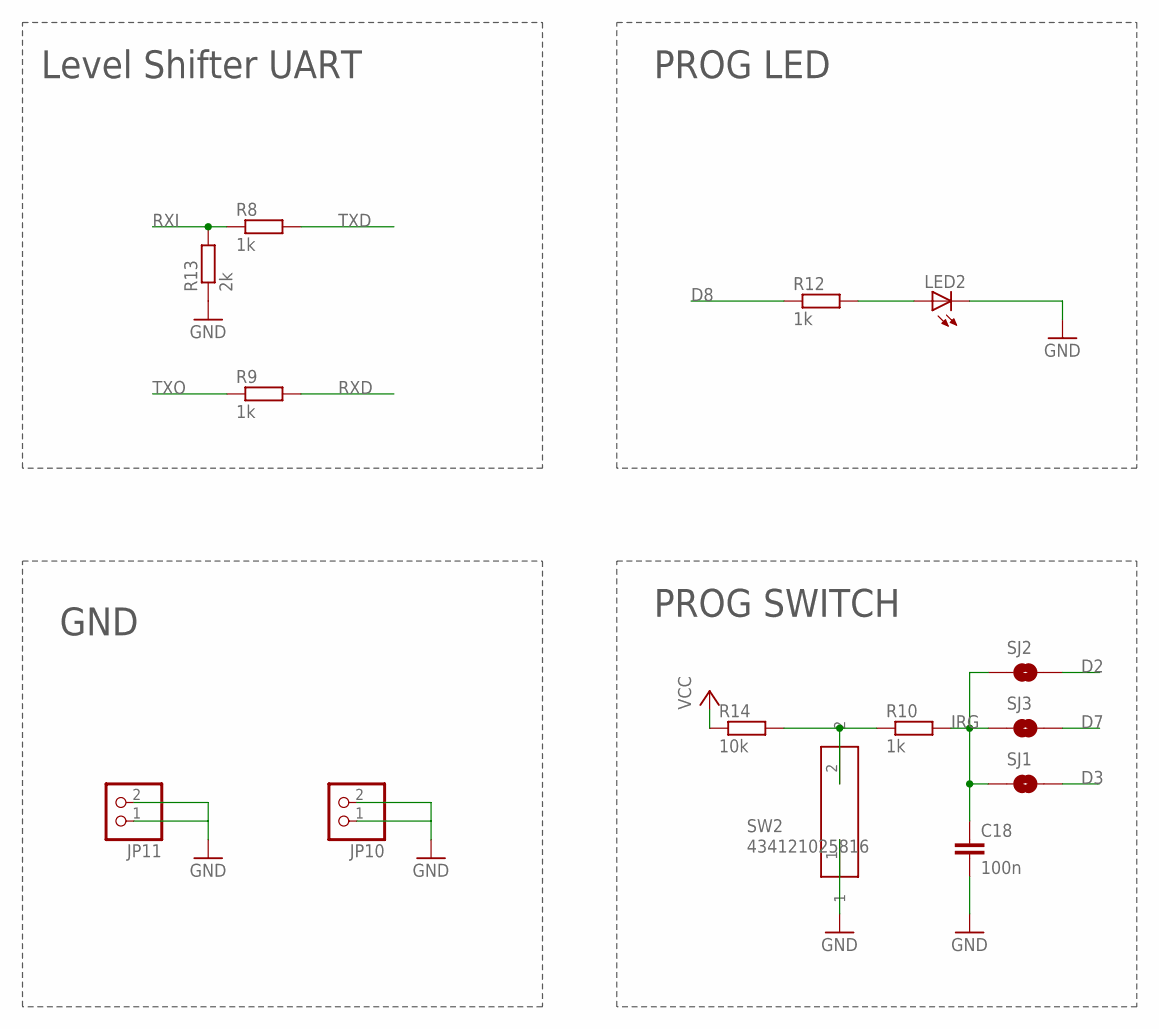
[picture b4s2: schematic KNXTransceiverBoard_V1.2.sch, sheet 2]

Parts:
C18: 100n; C0603
JP10, JP11: PINHD-1X2; 1X02
LED2: LEDCHIP-LED0805; CHIP-LED0805
R8, R10, R12: 1k; R0603
R9: 1k; R0805
R13: 2k; R0805
R14: 10k; R0603
SJ1, SJ2, SJ3: SOLDERJUMPERNC; SJ_2S
SW2: 434121025816

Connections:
D2: SJ2.2; also elsewhere on the board
D3: SJ1.2; also elsewhere on the board
D7: SJ3.2; also elsewhere on the board
D8: R12.1; also elsewhere on the board
GND: C18.2, JP10.1, JP10.2, JP11.1, JP11.2, LED2.C, R13.1, SW2.1; also elsewhere on the board
IRG: C18.1, R10.2, SJ1.1, SJ2.1, SJ3.1
unnamed: LED2.A, R12.2
unnamed: R10.1, R14.2, SW2.2
RXD: R9.2; also elsewhere on the board
RXI: R8.1, R13.2; also elsewhere on the board
TXD: R8.2; also elsewhere on the board
TXO: R9.1; also elsewhere on the board
VCC: R14.1; also elsewhere on the board

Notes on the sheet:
Level Shifter UART
PROG LED
GND
PROG SWITCH

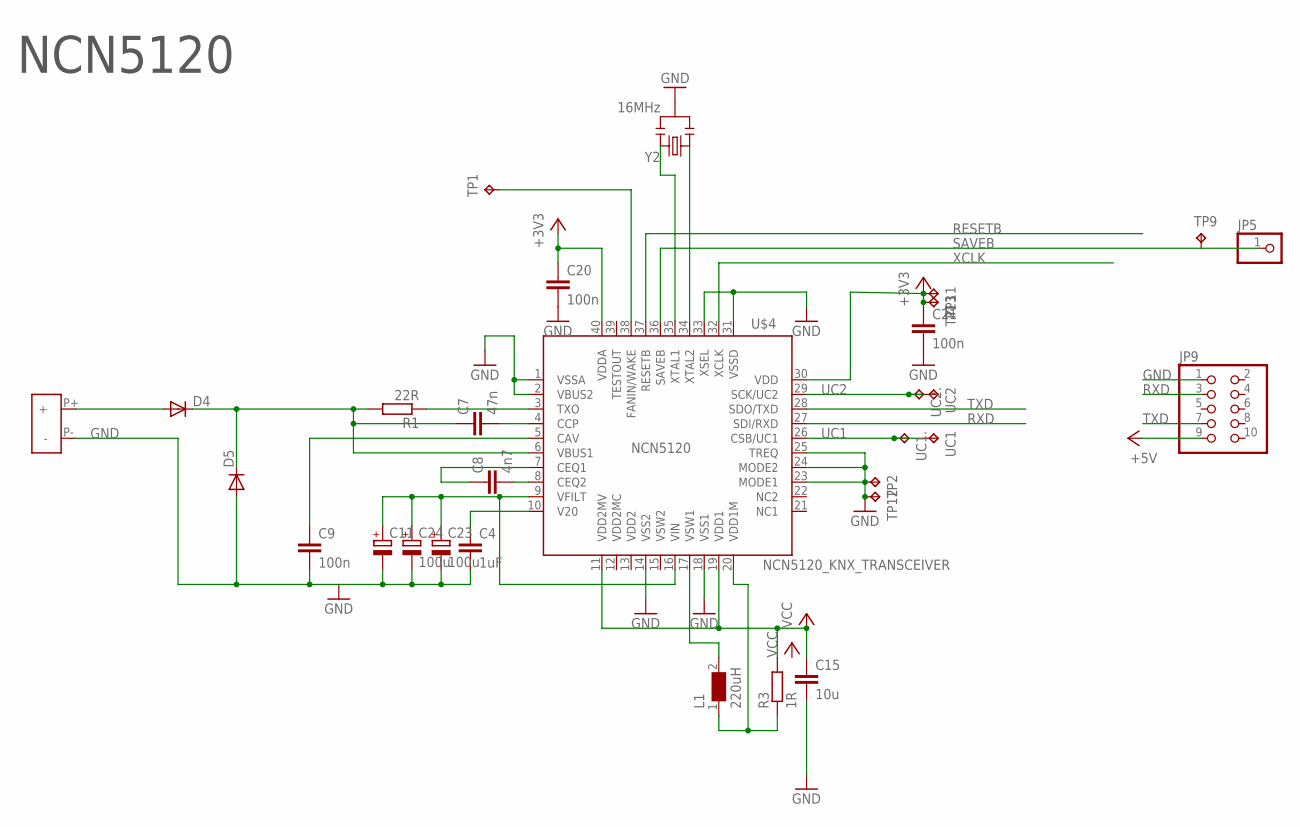
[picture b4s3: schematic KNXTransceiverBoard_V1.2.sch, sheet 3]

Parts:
C4: 1uF; C0603
C7: 47n; C0603
C8: 4n7; C0603
C9, C20, C21: 100n; C0603
C11: CPOL-EUE; PANASONIC_E
C15: 10u; C0805
C23, C24: 100u; SMC_D
D4, D5: DIODESMA-ALT; SMA-DIODE_ALT
JP5: PINHD-1X1; 1X01
JP9: PINHD-2X5; 2X05
L1: 220uH; WE-PD2_7850
R1: 22R; R2512
R3: 1R; R0603
TP1, TP9: TPTP10SQ; TP10SQ
TP2, TP11, TP12, TP13: TPTP09SQ; TP09SQ
U$2: KNX_KLEMME
U$4: NCN5120_KNX_TRANSCEIVER; QFN40
UC1, UC1., UC2, UC2.: TPTP09SQ; TP09SQ
Y2: 16MHz; RESONATOR-SMD

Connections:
GND: C4.2, C9.2, C11.-, C15.2, C20.2, C21.2, C23.-, C24.-, D5.A, JP9.1, TP2.TP, TP12.TP, U$2.P- (-), U$4.1 (VSSA), U$4.2 (VBUS2), U$4.14 (VSS2), U$4.18 (VSS1), U$4.23 (MODE1), U$4.24 (MODE2), U$4.25 (TREQ), U$4.31 (VSSD), U$4.33 (XSEL), Y2.2; also elsewhere on the board
unnamed: C7.1, D4.C, D5.C, R1.2, U$4.6 (VBUS1)
unnamed: C8.1, U$4.7 (CEQ1)
unnamed: C11.+, C23.+, C24.+, U$4.9 (VFILT), U$4.16 (VIN)
unnamed: C4.1, U$4.10 (V20)
unnamed: C7.2, U$4.4 (CCP)
unnamed: C9.1, U$4.5 (CAV)
unnamed: C8.2, U$4.8 (CEQ2)
unnamed: TP1.TP, U$4.38 (FANIN/WAKE)
unnamed: D4.A, U$2.P+ (+)
unnamed: L1.2, U$4.17 (VSW1)
unnamed: L1.1, R3.1, U$4.20 (VDD1M)
unnamed: R1.1, U$4.3 (TXO)
RAW: JP9.9; also elsewhere on the board
RESETB: U$4.37 (RESETB)
RXD: JP9.3, U$4.27 (SDI/RXD); also elsewhere on the board
SAVEB: JP5.1, TP9.TP, U$4.36 (SAVEB)
TXAL1: U$4.35 (XTAL1), Y2.3
TXAL2: U$4.34 (XTAL2), Y2.1
TXD: JP9.7, U$4.28 (SDO/TXD); also elsewhere on the board
UC1: U$4.26 (CSB/UC1), UC1.TP, UC1..TP
UC2: U$4.29 (SCK/UC2), UC2.TP, UC2..TP
VCC: C15.1, C20.1, C21.1, R3.2, TP11.TP, TP13.TP, U$4.11 (VDD2MV), U$4.19 (VDD1), U$4.30 (VDD), U$4.40 (VDDA); also elsewhere on the board
XCLK: U$4.32 (XCLK)

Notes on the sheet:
NCN5120

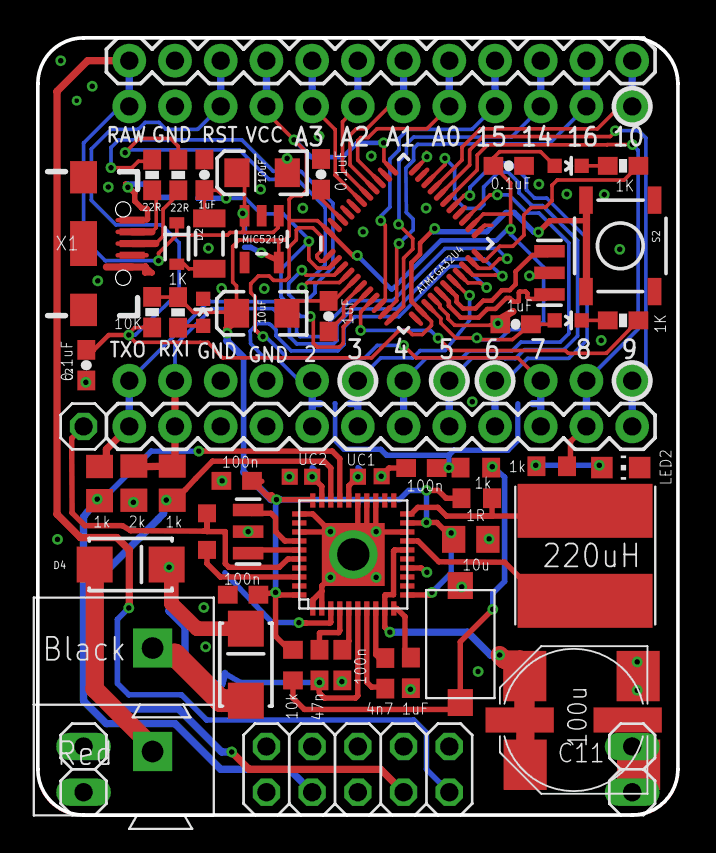
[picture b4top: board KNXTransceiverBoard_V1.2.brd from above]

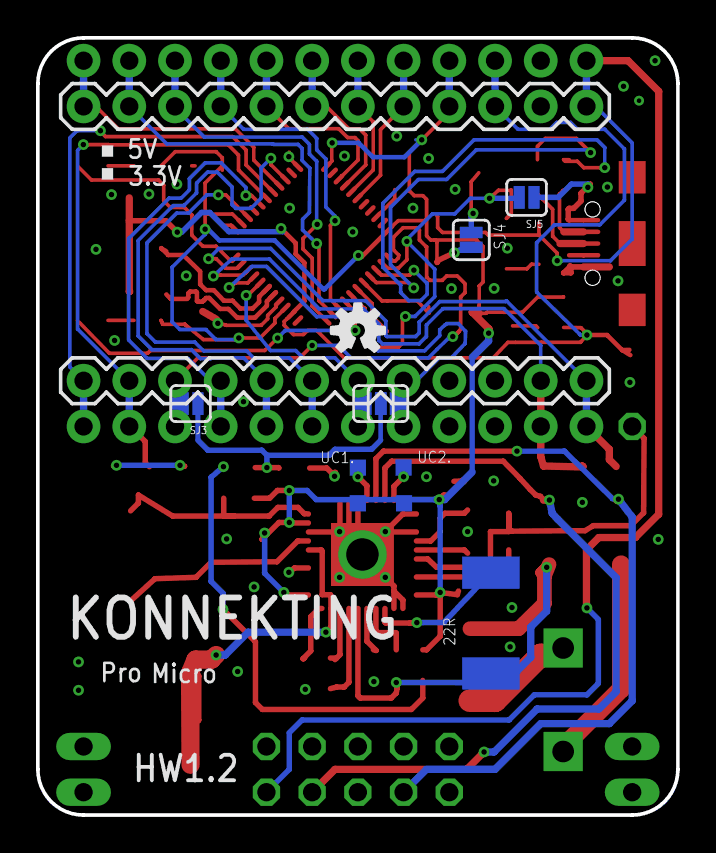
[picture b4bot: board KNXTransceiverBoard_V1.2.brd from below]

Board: 2 copper layers, 35.6 x 43.2 mm, 76 parts (13 on the bottom side), 60 nets.

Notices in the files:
parts and their libraries:
SparkFun-Aesthetics: Licensing: CC v3.0 Share-Alike You are welcome to use this library for commercial purposes.
Wuerth_Kurzhubtaster: Copyright: Würth Elektronik
SparkFun-Connectors: Licensing: Creative Commons ShareAlike 4.0 International - https://creativecommons.org/licenses/by-sa/4.0
